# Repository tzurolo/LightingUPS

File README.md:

# LED Lighting UPS

The LED Lighting UPS system provides backup lighting for a study room when the AC power goes down.

It can also be used as the primary lighting source for a room that has no existing AC-powered lighting.

Being a UPS, it auto-switches to its internal battery when the AC power goes down, and back to AC when
it comes back up. While the AC power is on it keeps the battery charged.

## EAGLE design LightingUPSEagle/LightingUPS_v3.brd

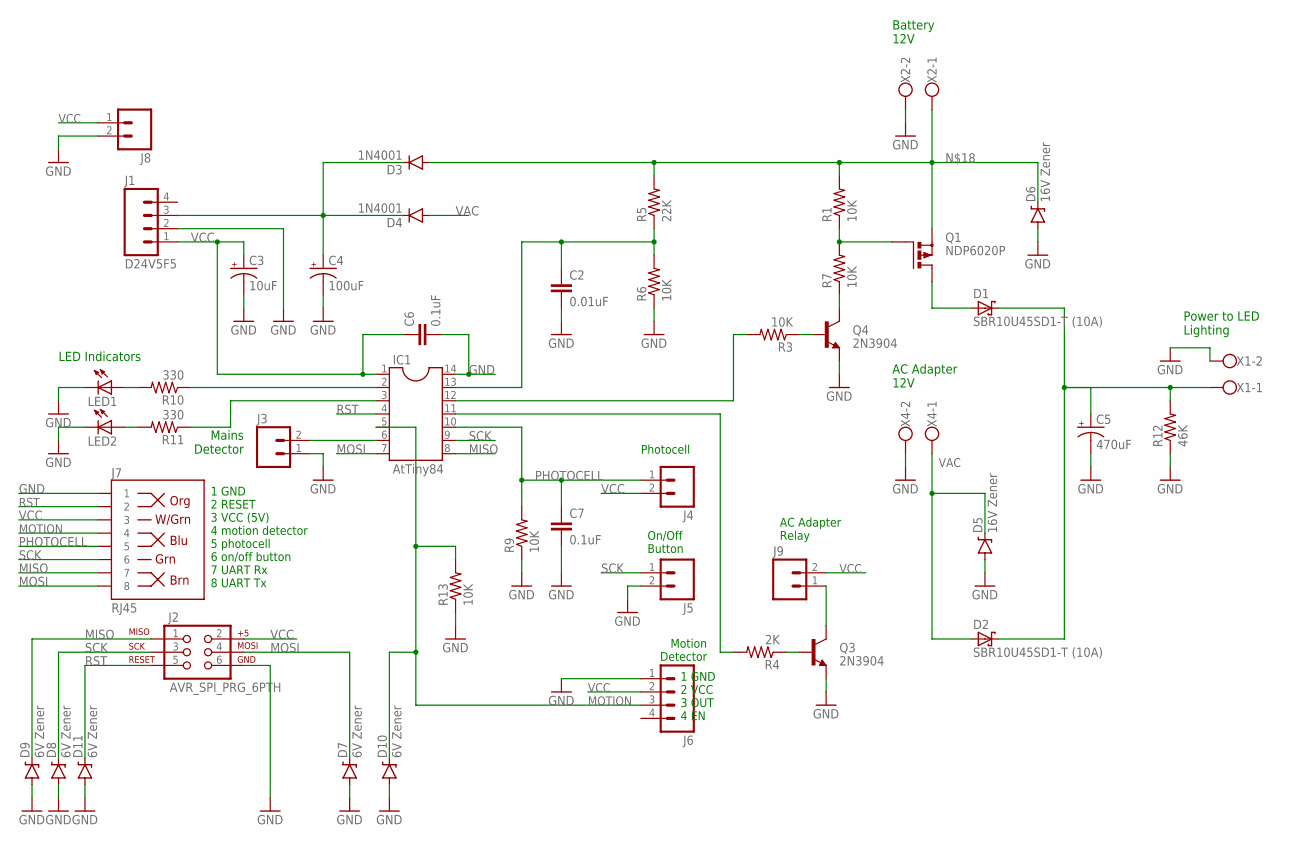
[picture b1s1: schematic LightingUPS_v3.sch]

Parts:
C2: 0.01uF; CAP-PTH-5MM
C3: 10uF; CPOL-RADIAL-100UF-25V
C4: 100uF; CPOL-RADIAL-100UF-25V
C5: 470uF; CPOL-RADIAL-1000UF-25V
C6, C7: 0.1uF; CAP-PTH-SMALL
D1, D2: SBR10U45SD1-T (10A); DO201T15
D3, D4: 1N4001; DIODE-1N4001
D5, D6: 16V Zener; DIODE-ZENER
D7, D8, D9, D10, D11: 6V Zener; DIODE-ZENER
IC1: AtTiny84; DIL14
J1: D24V5F5; 1X04
J2: AVR_SPI_PRG_6PTH; 2X3
J3, J4, J5, J8, J9: M02PTH; 1X02
J6: M04PTH; 1X04
J7: RJ45; RJ45-8
LED1, LED2: LED5MM
Q1: NDP6020P; TO220BV
Q3, Q4: 2N3904; TO-92-AMMO
R1, R3, R6, R7, R9, R13: 10K; 0204/5
R4: 2K; 0204/5
R5: 22K; 0204/5
R10, R11: 330; 0204/5
R12: 46K; 0204/5
X1, X2, X4: W237-102

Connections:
GND: C2.2, C3.2 (-), C4.2 (-), C5.-, C6.2, C7.2, D5.P$2 (A), D6.P$2 (A), D7.P$2 (A), D8.P$2 (A), D9.P$2 (A), D10.P$2 (A), D11.P$2 (A), IC1.14, J1.2, J2.6, J3.1, J5.2, J6.1, J7.1, J8.2, LED1.K (C), LED2.K (C), Q3.1 (E), Q4.1 (E), R6.1, R9.1, R12.1, R13.1, X1.2, X2.2, X4.2
MISO: D9.P$1 (C), IC1.8, J2.1, J7.7
MOSI: D7.P$1 (C), IC1.7, J2.4, J7.8
MOTION: D10.P$1 (C), IC1.5, J6.3, J7.4, R13.2
unnamed: LED1.A, R10.2
unnamed: Q1.G, R1.1, R7.2
unnamed: Q4.2 (B), R3.1
unnamed: D1.A, Q1.D
unnamed: C5.+, D1.C, D2.C, R12.2, X1.1
unnamed: C2.1, IC1.13, R5.1, R6.2
unnamed: IC1.6, J3.2
unnamed: IC1.11, R4.2
unnamed: Q3.2 (B), R4.1
unnamed: IC1.12, R3.2
unnamed: C4.1 (+), D3.C, D4.C, J1.3
unnamed: Q4.3 (C), R7.1
unnamed: IC1.2, R10.1
unnamed: IC1.3, R11.1
unnamed: LED2.A, R11.2
unnamed: D3.A, D6.P$1 (C), Q1.S, R1.2, R5.2, X2.1
unnamed: J9.1, Q3.3 (C)
PHOTOCELL: C7.1, IC1.10, J4.1, J7.5, R9.2
RST: D11.P$1 (C), IC1.4, J2.5, J7.2
SCK: D8.P$1 (C), IC1.9, J2.3, J5.1, J7.6
VAC: D2.A, D4.A, D5.P$1 (C), X4.1
VCC: C3.1 (+), C6.1, IC1.1, J1.1, J2.2, J4.2, J6.2, J7.3, J8.1, J9.2

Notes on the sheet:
Battery 12V
AC Adapter 12V
LED Indicators
Power to LED Lighting
Mains Detector
1 GND 2 RESET 3 VCC (5V) 4 motion detector 5 photocell 6 on/off button 7 UART Rx 8 UART Tx
1 GND 2 VCC 3 OUT 4 EN
Photocell
Motion Detector
On/Off Button
AC Adapter Relay

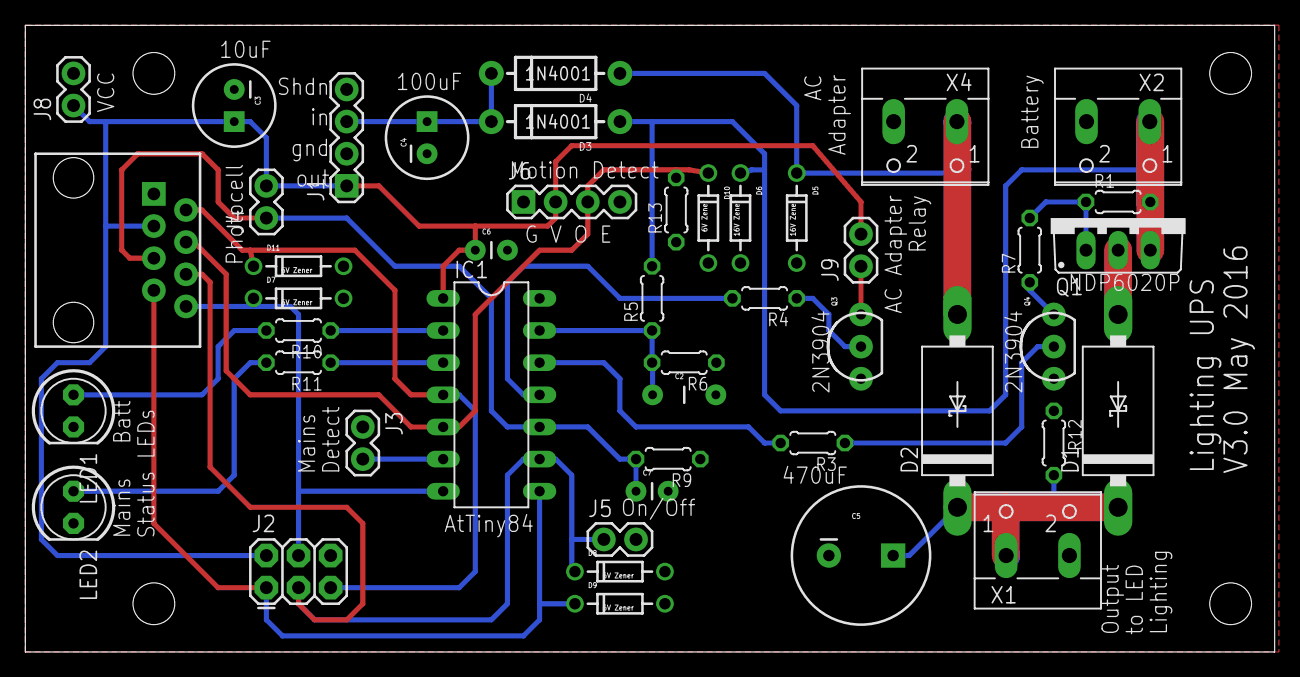
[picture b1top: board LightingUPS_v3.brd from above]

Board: 2 copper layers, 98.7 x 49.5 mm, 50 parts (0 on the bottom side), 26 nets.

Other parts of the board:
U$1, U$2, U$3, U$4: STAND-OFF

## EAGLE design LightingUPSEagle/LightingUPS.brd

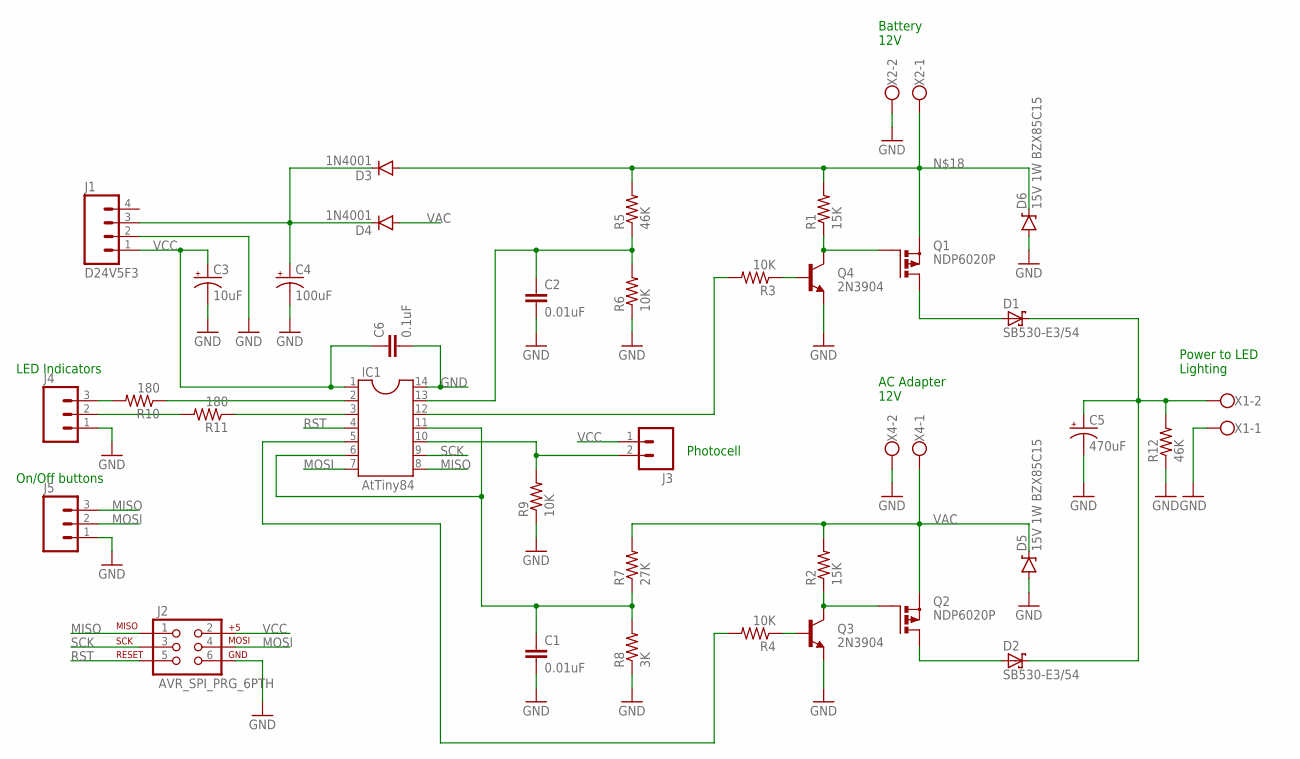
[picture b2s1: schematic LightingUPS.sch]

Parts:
C1, C2: 0.01uF; CAP-PTH-5MM
C3: 10uF; CPOL-RADIAL-100UF-25V
C4: 100uF; CPOL-RADIAL-100UF-25V
C5: 470uF; CPOL-RADIAL-1000UF-25V
C6: 0.1uF; CAP-PTH-SMALL
D1, D2: SB530-E3/54; DO201T15
D3, D4: 1N4001; DIODE-1N4001
D5, D6: 15V 1W BZX85C15; DIODE-ZENER
IC1: AtTiny84; DIL14
J1: D24V5F3; 1X04
J2: AVR_SPI_PRG_6PTH; 2X3
J3: M02PTH; 1X02
J4, J5: M03PTH; 1X03
Q1, Q2: NDP6020P; TO220BV
Q3, Q4: 2N3904; TO-92-AMMO
R1, R2: 15K; 0204/5
R3, R4, R6, R9: 10K; 0204/5
R5, R12: 46K; 0204/5
R7: 27K; 0204/5
R8: 3K; 0204/5
R10, R11: 180; 0204/5
X1, X2, X4: W237-102

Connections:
GND: C1.2, C2.2, C3.2 (-), C4.2 (-), C5.-, C6.2, D5.P$2 (A), D6.P$2 (A), IC1.14, J1.2, J2.6, J4.1, J5.1, Q3.1 (E), Q4.1 (E), R6.1, R8.1, R9.1, R12.1, X1.1, X2.2, X4.2
MISO: IC1.8, J2.1, J5.3
MOSI: IC1.7, J2.4, J5.2
unnamed: J4.3, R10.2
unnamed: Q1.G, Q4.3 (C), R1.1
unnamed: Q4.2 (B), R3.1
unnamed: D1.A, Q1.D
unnamed: C5.+, D1.C, D2.C, R12.2, X1.2
unnamed: C2.1, IC1.13, R5.1, R6.2
unnamed: IC1.10, J3.2, R9.2
unnamed: C1.1, IC1.6, IC1.11, R7.1, R8.2
unnamed: Q2.G, Q3.3 (C), R2.1
unnamed: Q3.2 (B), R4.1
unnamed: D2.A, Q2.D
unnamed: IC1.12, R3.2
unnamed: C4.1 (+), D3.C, D4.C, J1.3
unnamed: IC1.5, R4.2
unnamed: IC1.2, R10.1
unnamed: IC1.3, R11.1
unnamed: J4.2, R11.2
unnamed: D3.A, D6.P$1 (C), Q1.S, R1.2, R5.2, X2.1
RST: IC1.4, J2.5
SCK: IC1.9, J2.3
VAC: D4.A, D5.P$1 (C), Q2.S, R2.2, R7.2, X4.1
VCC: C3.1 (+), C6.1, IC1.1, J1.1, J2.2, J3.1

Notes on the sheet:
Photocell
Battery 12V
AC Adapter 12V
LED Indicators
On/Off buttons
Power to LED Lighting

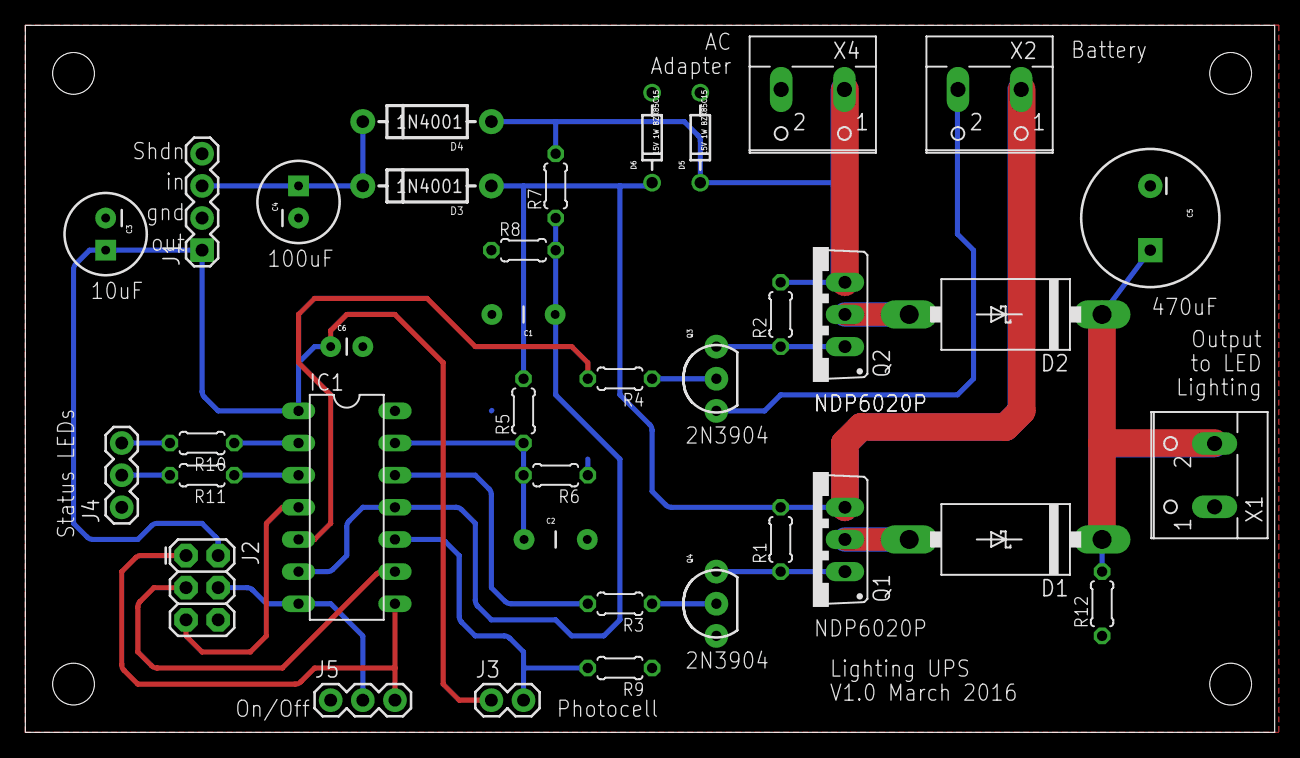
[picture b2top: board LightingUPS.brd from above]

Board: 2 copper layers, 98.7 x 55.9 mm, 41 parts (0 on the bottom side), 25 nets.

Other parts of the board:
U$1, U$2, U$3, U$4: STAND-OFF

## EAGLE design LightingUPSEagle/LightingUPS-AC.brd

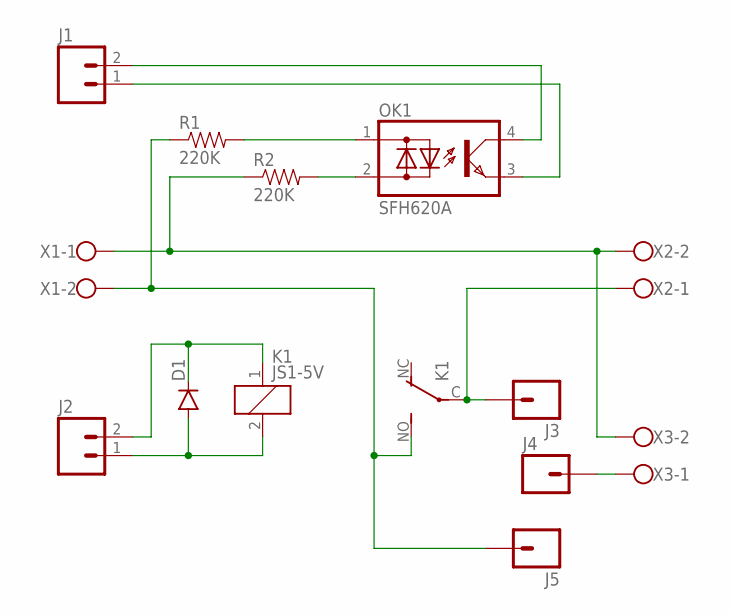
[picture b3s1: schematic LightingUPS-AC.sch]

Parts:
D1: DIODEPTH; DIODE-1N4001
J1, J2: M02PTH; 1X02
J3, J4, J5: M01PTH; 1X01
K1: JS1-5V; JS-M
OK1: SFH620A; DIL04
R1, R2: 220K; AXIAL-0.4
X1, X2, X3: W237-102

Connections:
unnamed: J4.1, X3.1
unnamed: J1.1, OK1.3 (E)
unnamed: J3.1, K1.C, X2.1
unnamed: D1.A, J2.1, K1.2
unnamed: D1.C, J2.2, K1.1
unnamed: J1.2, OK1.4 (C)
unnamed: OK1.2 (AC2), R2.P$2 (2)
unnamed: OK1.1 (AC1), R1.P$2 (2)
unnamed: R2.P$1 (1), X1.1, X2.2, X3.2
unnamed: J5.1, K1.NO (S), R1.P$1 (1), X1.2

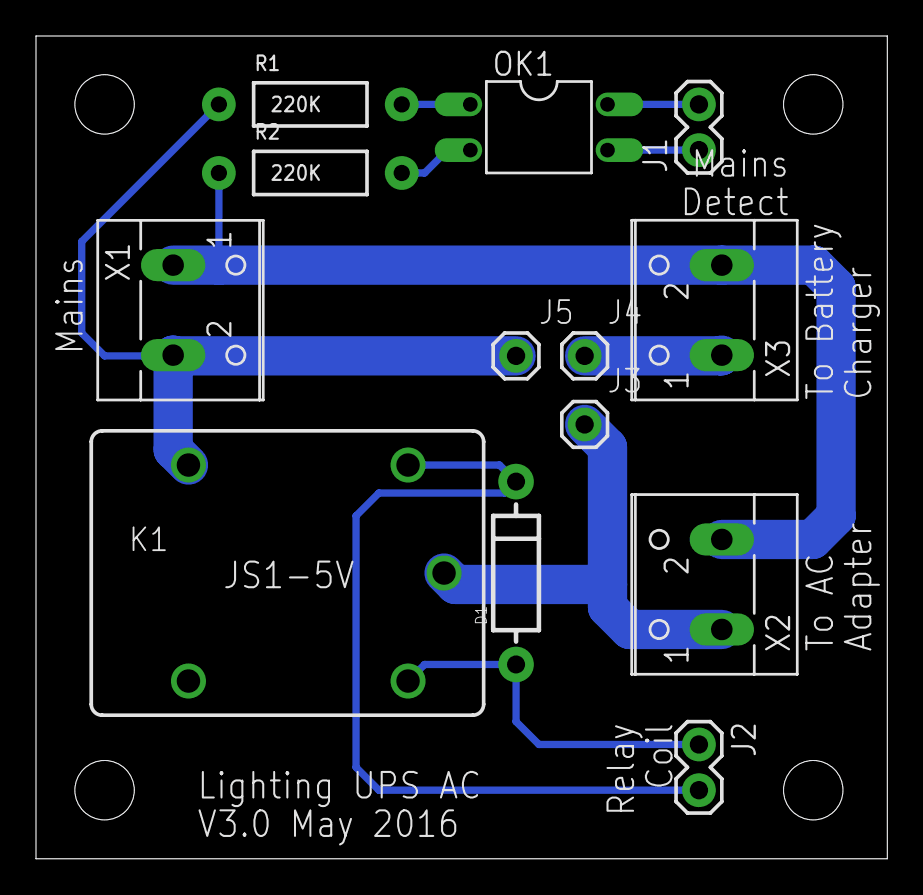
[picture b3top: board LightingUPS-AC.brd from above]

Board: 2 copper layers, 47.3 x 45.7 mm, 17 parts (0 on the bottom side), 10 nets.

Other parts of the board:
U$1, U$2, U$3, U$4: STAND-OFF

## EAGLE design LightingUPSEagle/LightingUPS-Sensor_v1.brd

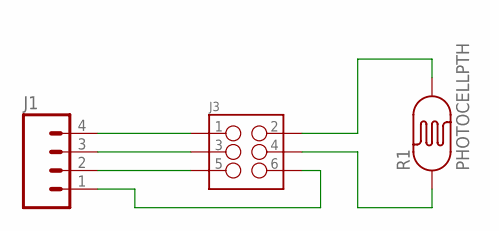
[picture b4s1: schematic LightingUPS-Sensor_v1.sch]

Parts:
J1: M04PTH; 1X04
J3: M03X2SHROUD; 2X3-SHROUDED
R1: PHOTOCELLPTH; PHOTOCELL

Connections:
unnamed: J3.4, R1.1
unnamed: J3.2, R1.2
unnamed: J1.4, J3.1
unnamed: J1.3, J3.3
unnamed: J1.2, J3.5
unnamed: J1.1, J3.6

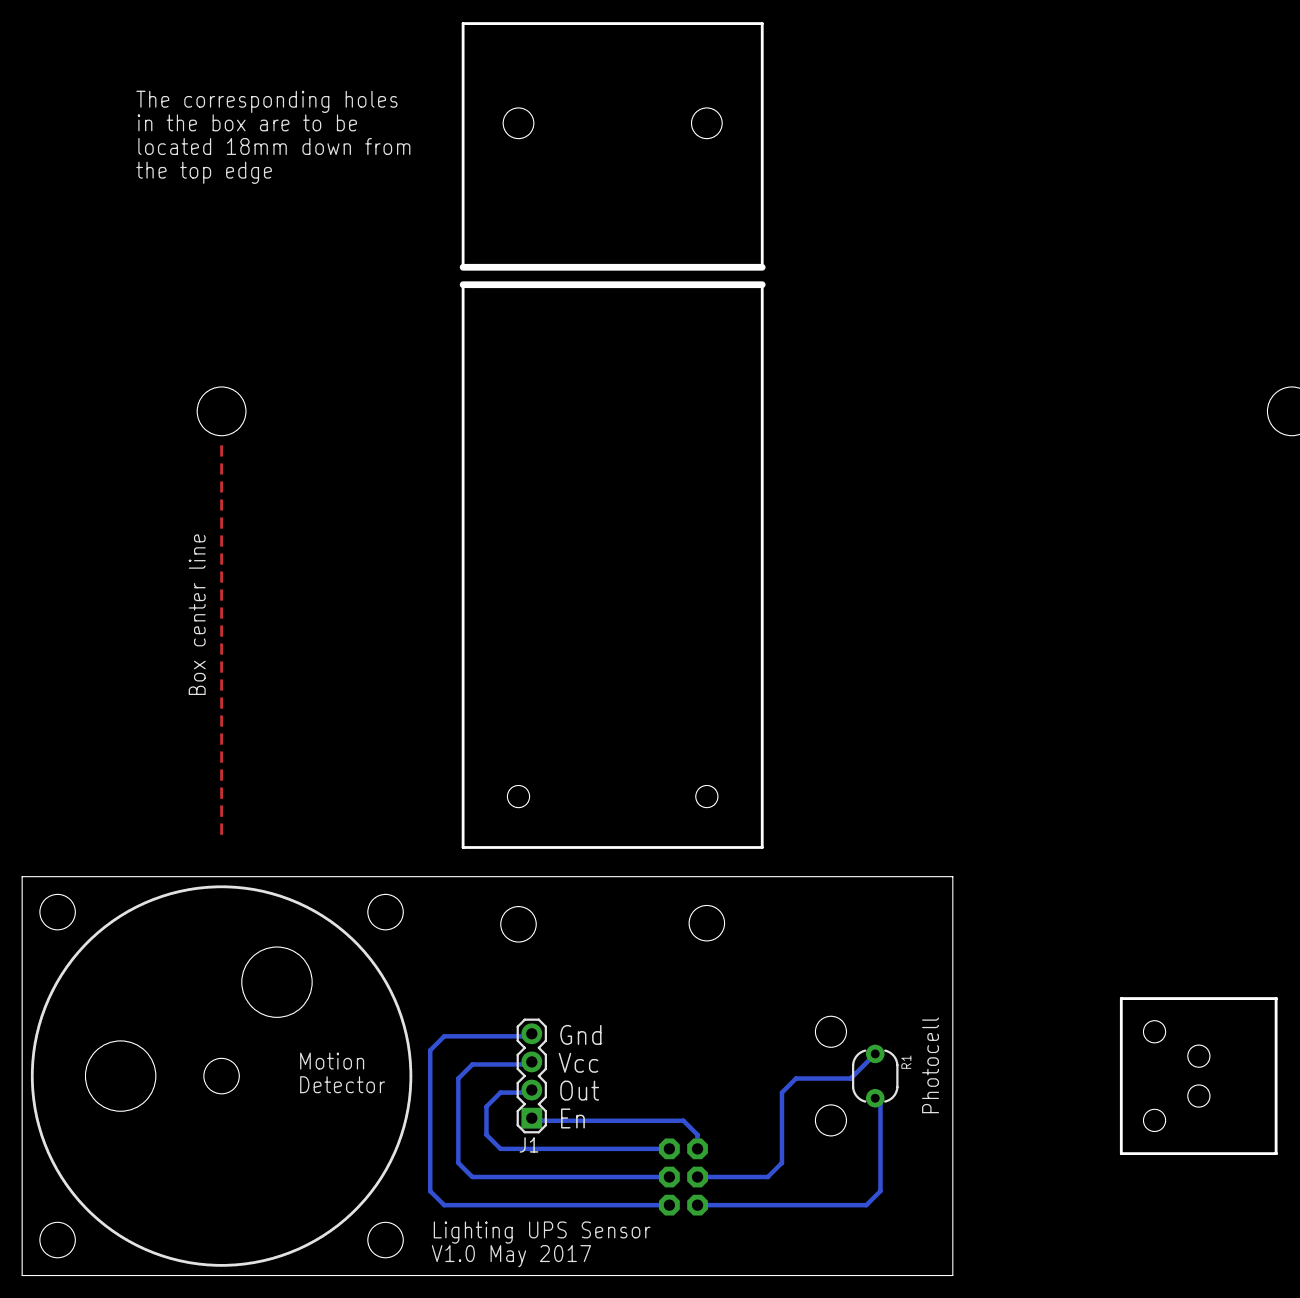
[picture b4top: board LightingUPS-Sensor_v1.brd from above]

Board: 2 copper layers, 113.2 x 113.0 mm, 5 parts (1 on the bottom side), 6 nets.

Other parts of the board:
U$1, U$5: DRILL_0.2500

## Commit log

2017-09-11 Create placeholder
2017-10-12 first level implementatin
2017-10-31 prototype of firmware reflash
    invokes avrdude using child_process in node.js
2017-11-02 full cycle reflash, settings
    reflash integrates with monitoring
    ability to change settings
    supports V1.0 firmware
2017-11-02 command response changes to support node monitor
2017-11-07 index.js now launches browser
2017-11-07 call node.js setup instead of including inline

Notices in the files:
parts and their libraries:
SparkFun-DiscreteSemi: Licensing: Creative Commons ShareAlike 4.0 International - https://creativecommons.org/licenses/by-sa/4.0
